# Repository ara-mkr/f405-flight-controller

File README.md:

# F405 Flight Controller

This is a flight controller I designed as a side project. It was fun and pretty challenging, and I'm planning to build a drone with it at some point!

## The design

I did the schematic and layout in KiCad, and wrote some Python scripts to check the connections and spit out the manufacturing files.

It's built around an STM32F405. It reads the gyro and barometer and sends signals out to the ESCs. It also has its own power regulators and plugs for a receiver, GPS, and camera.

I haven't gotten it made or flown yet, so there's still a lot of building and testing to do. If you want to order one, here's [how I'd do it](HOW_TO_ORDER.md).

<table>
<tr>
<td width="50%"><br>Angled view</td>
<td width="50%"><br>Bottom view</td>
</tr>
<tr>
<td><br>Copper layers</td>
<td><br><a href="production/fc_f405_schematic.pdf">Schematic</a></td>
</tr>
</table>

Design files are in [hardware/](hardware/) and the manufacturing stuff is in [production/](production/).

Licensed under [CERN-OHL-P-2.0](LICENSE).

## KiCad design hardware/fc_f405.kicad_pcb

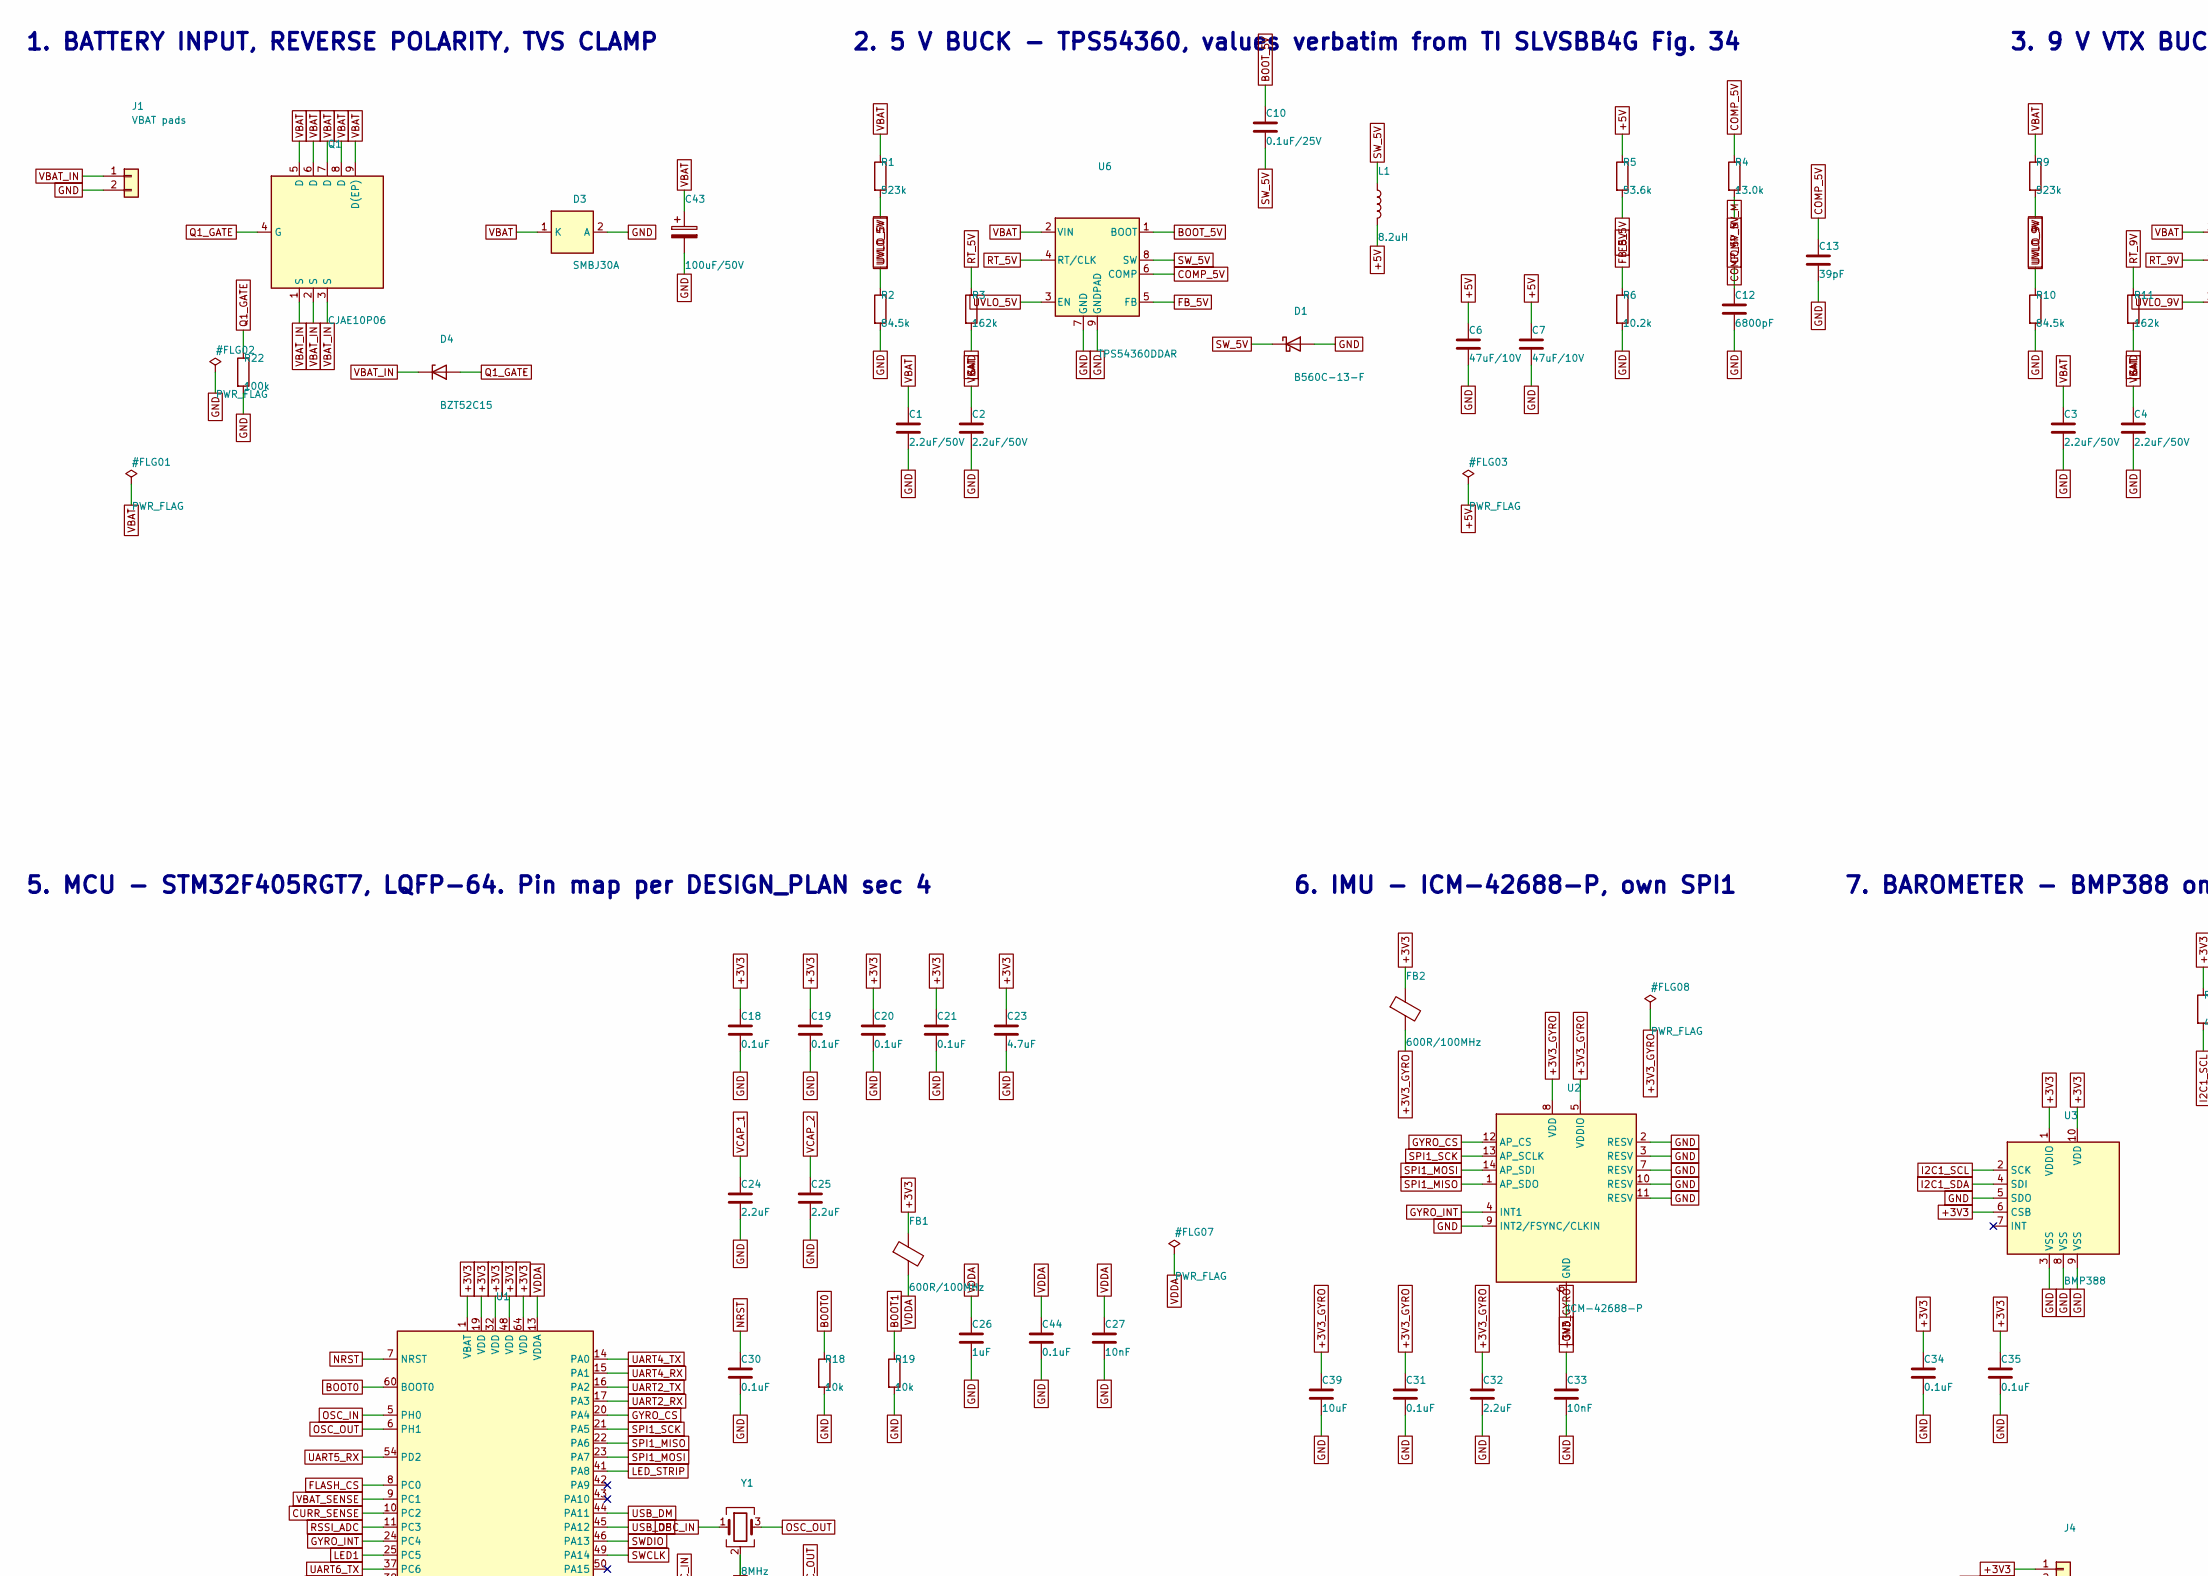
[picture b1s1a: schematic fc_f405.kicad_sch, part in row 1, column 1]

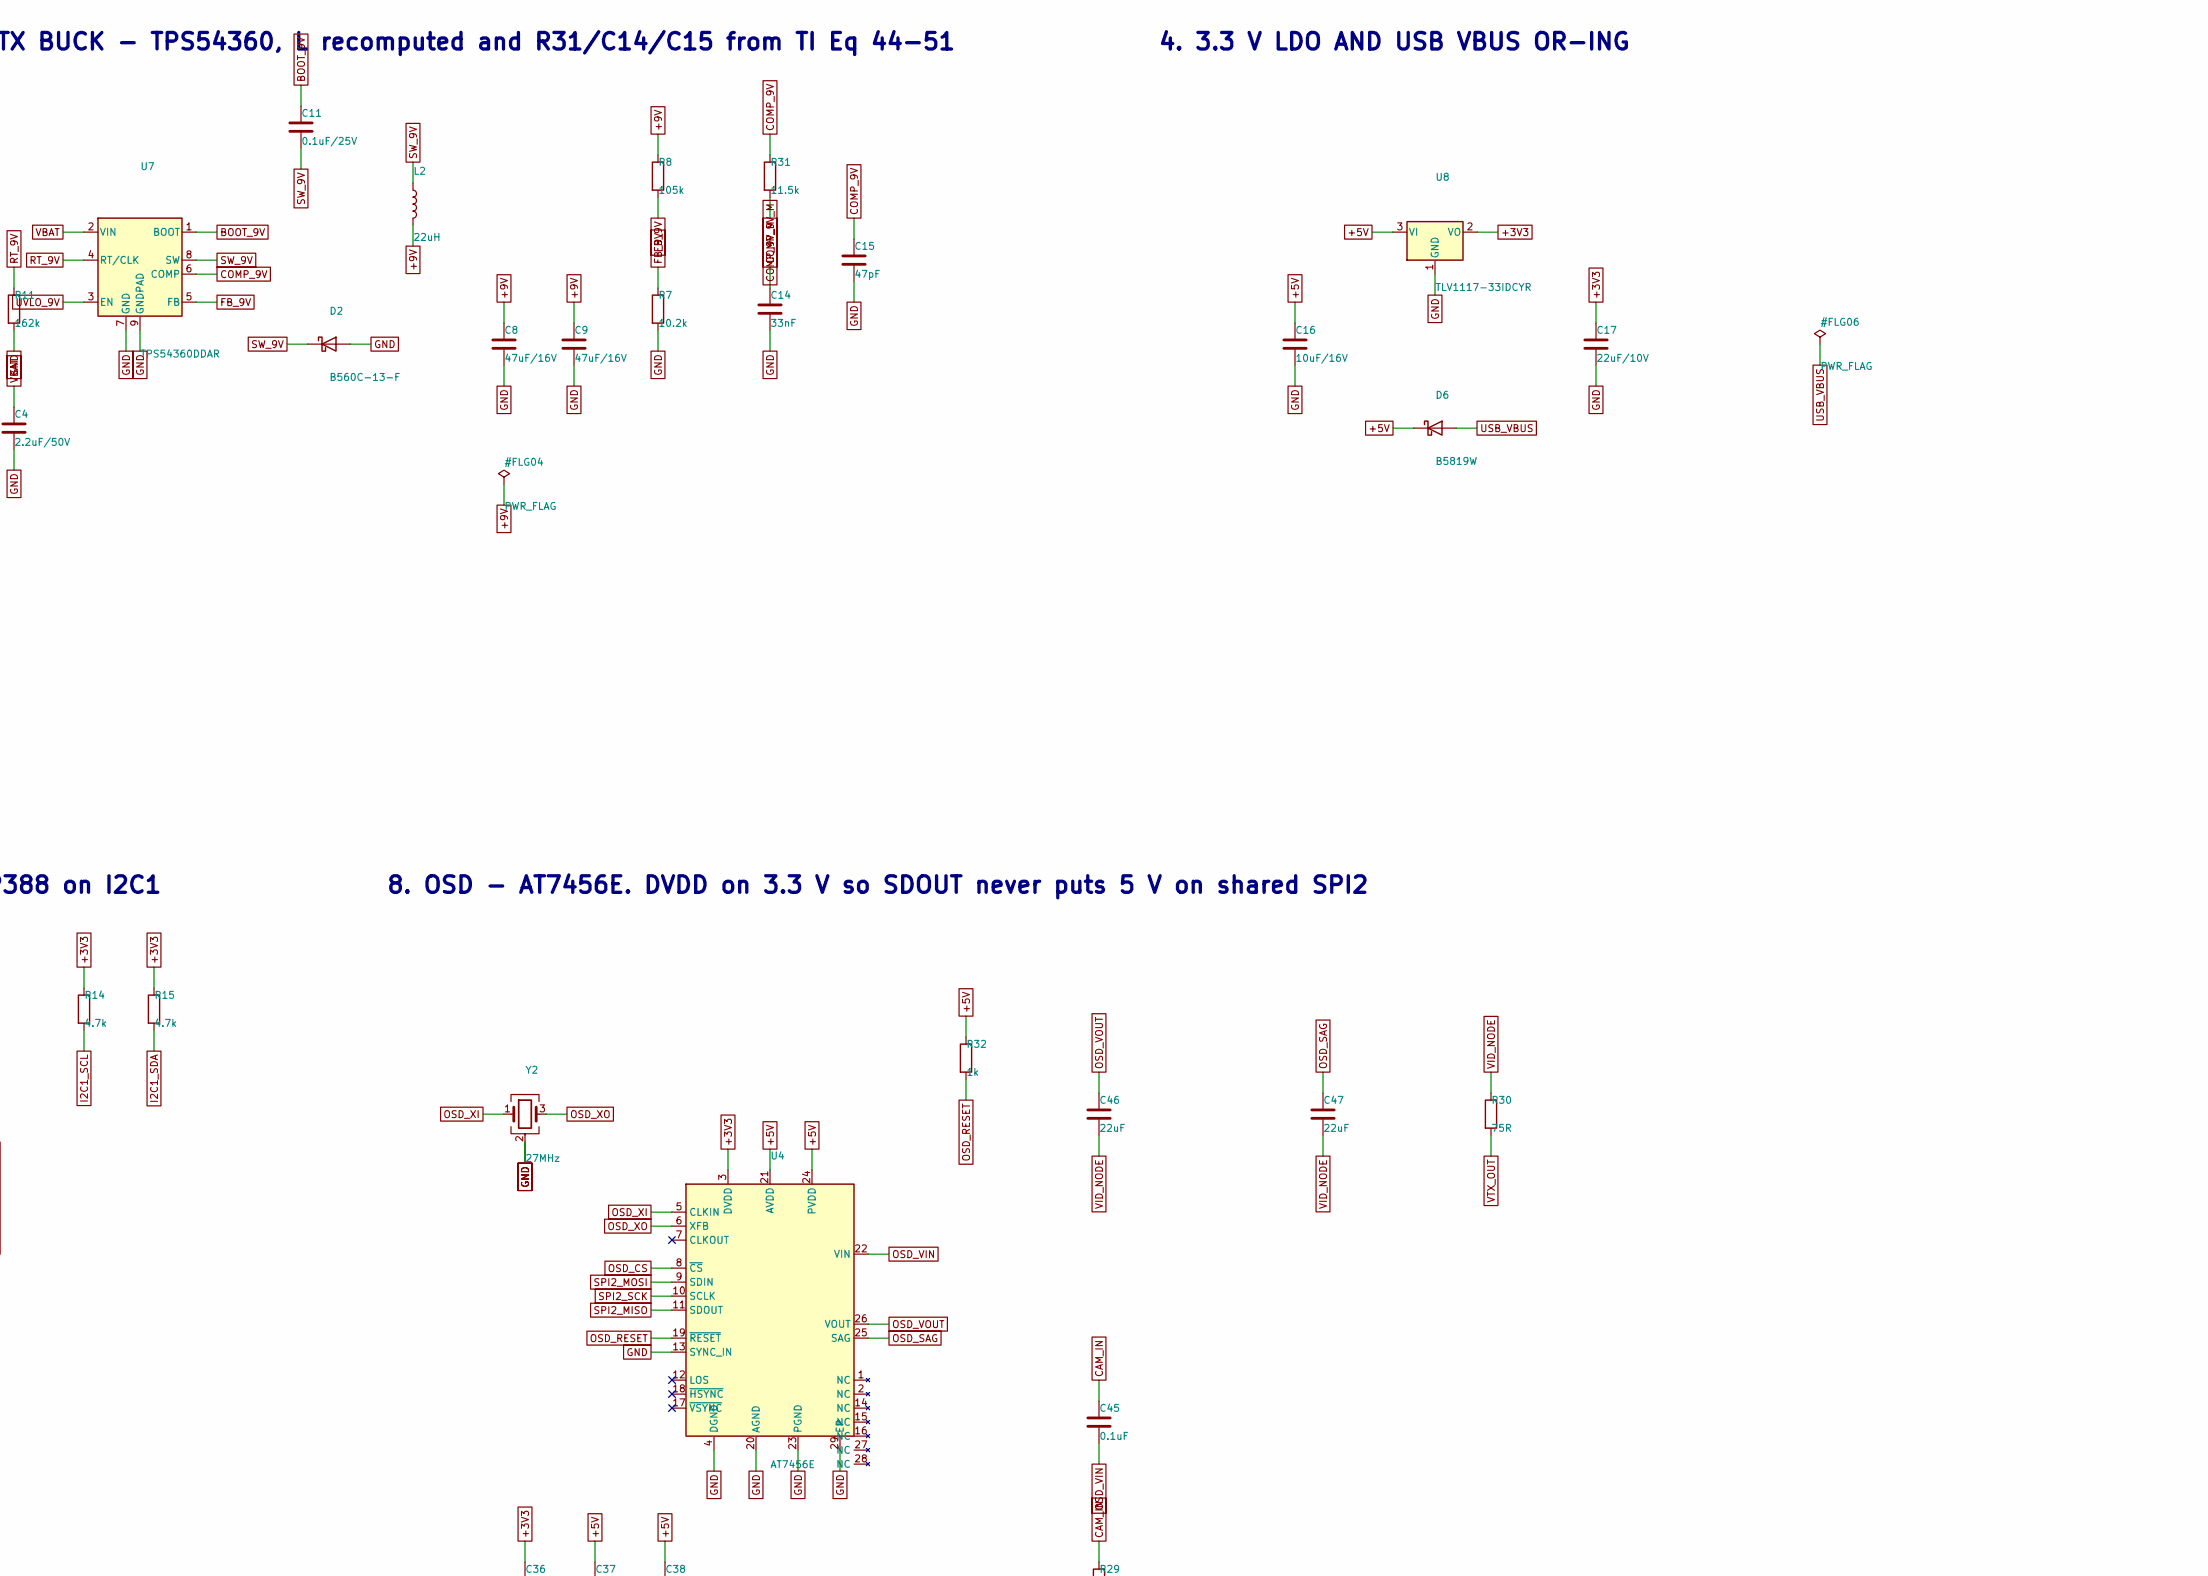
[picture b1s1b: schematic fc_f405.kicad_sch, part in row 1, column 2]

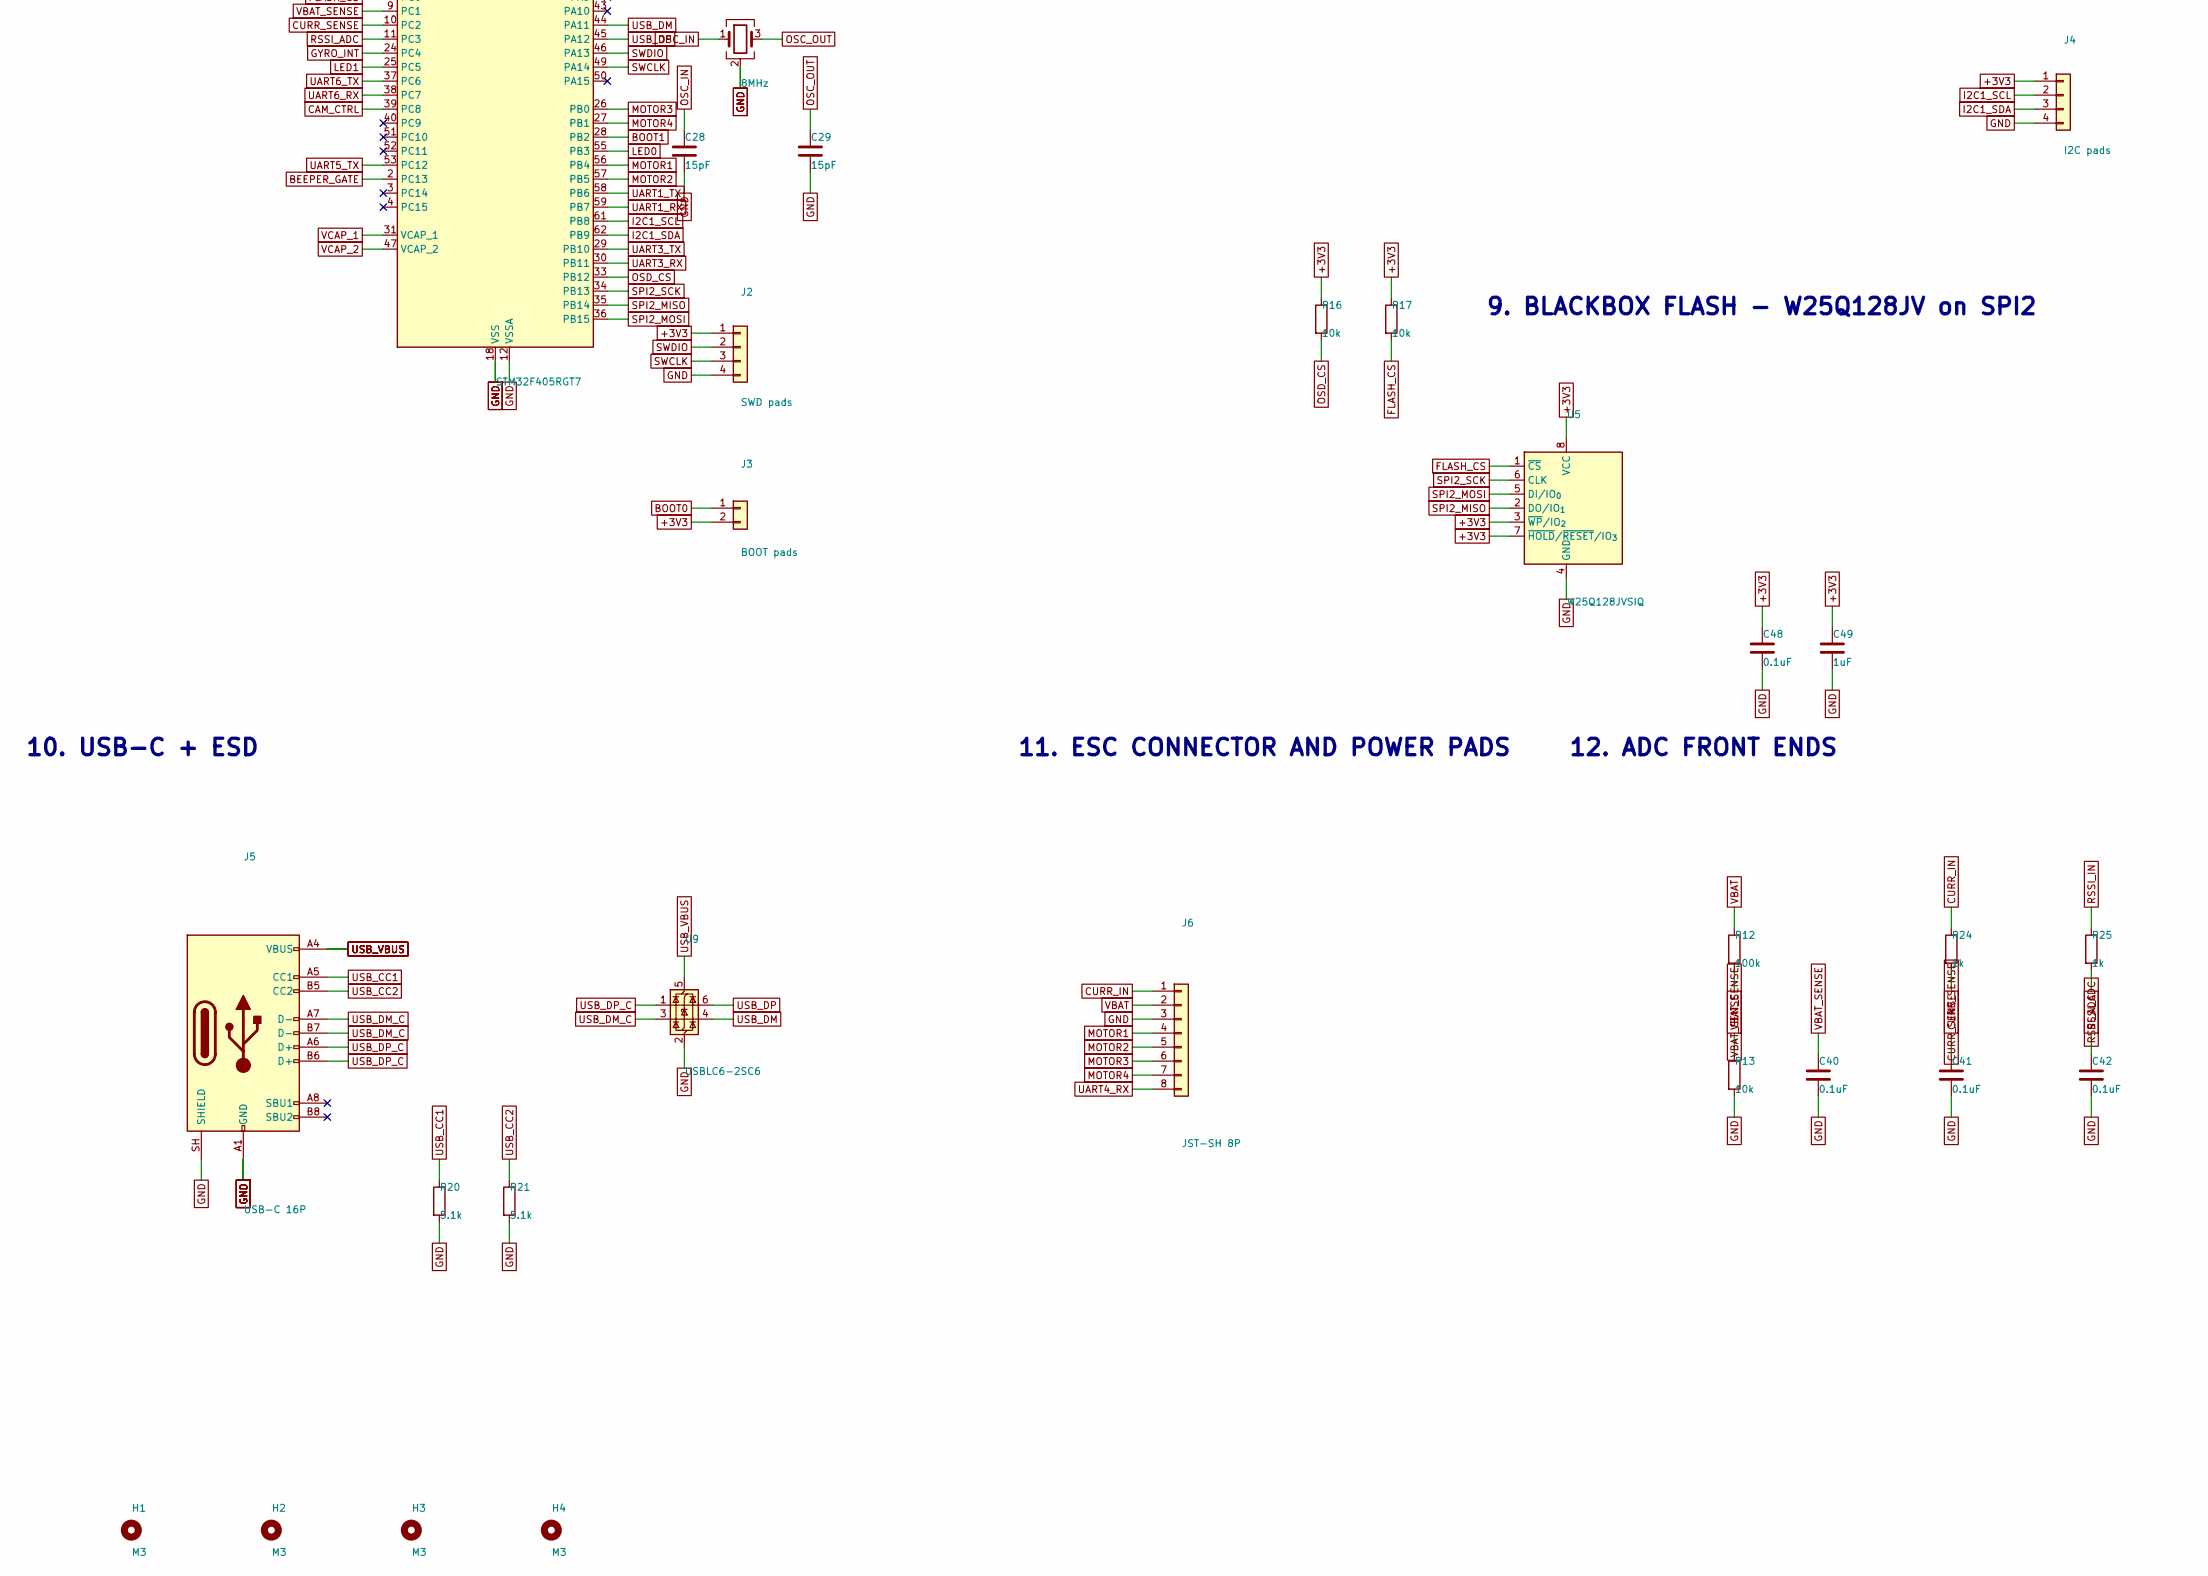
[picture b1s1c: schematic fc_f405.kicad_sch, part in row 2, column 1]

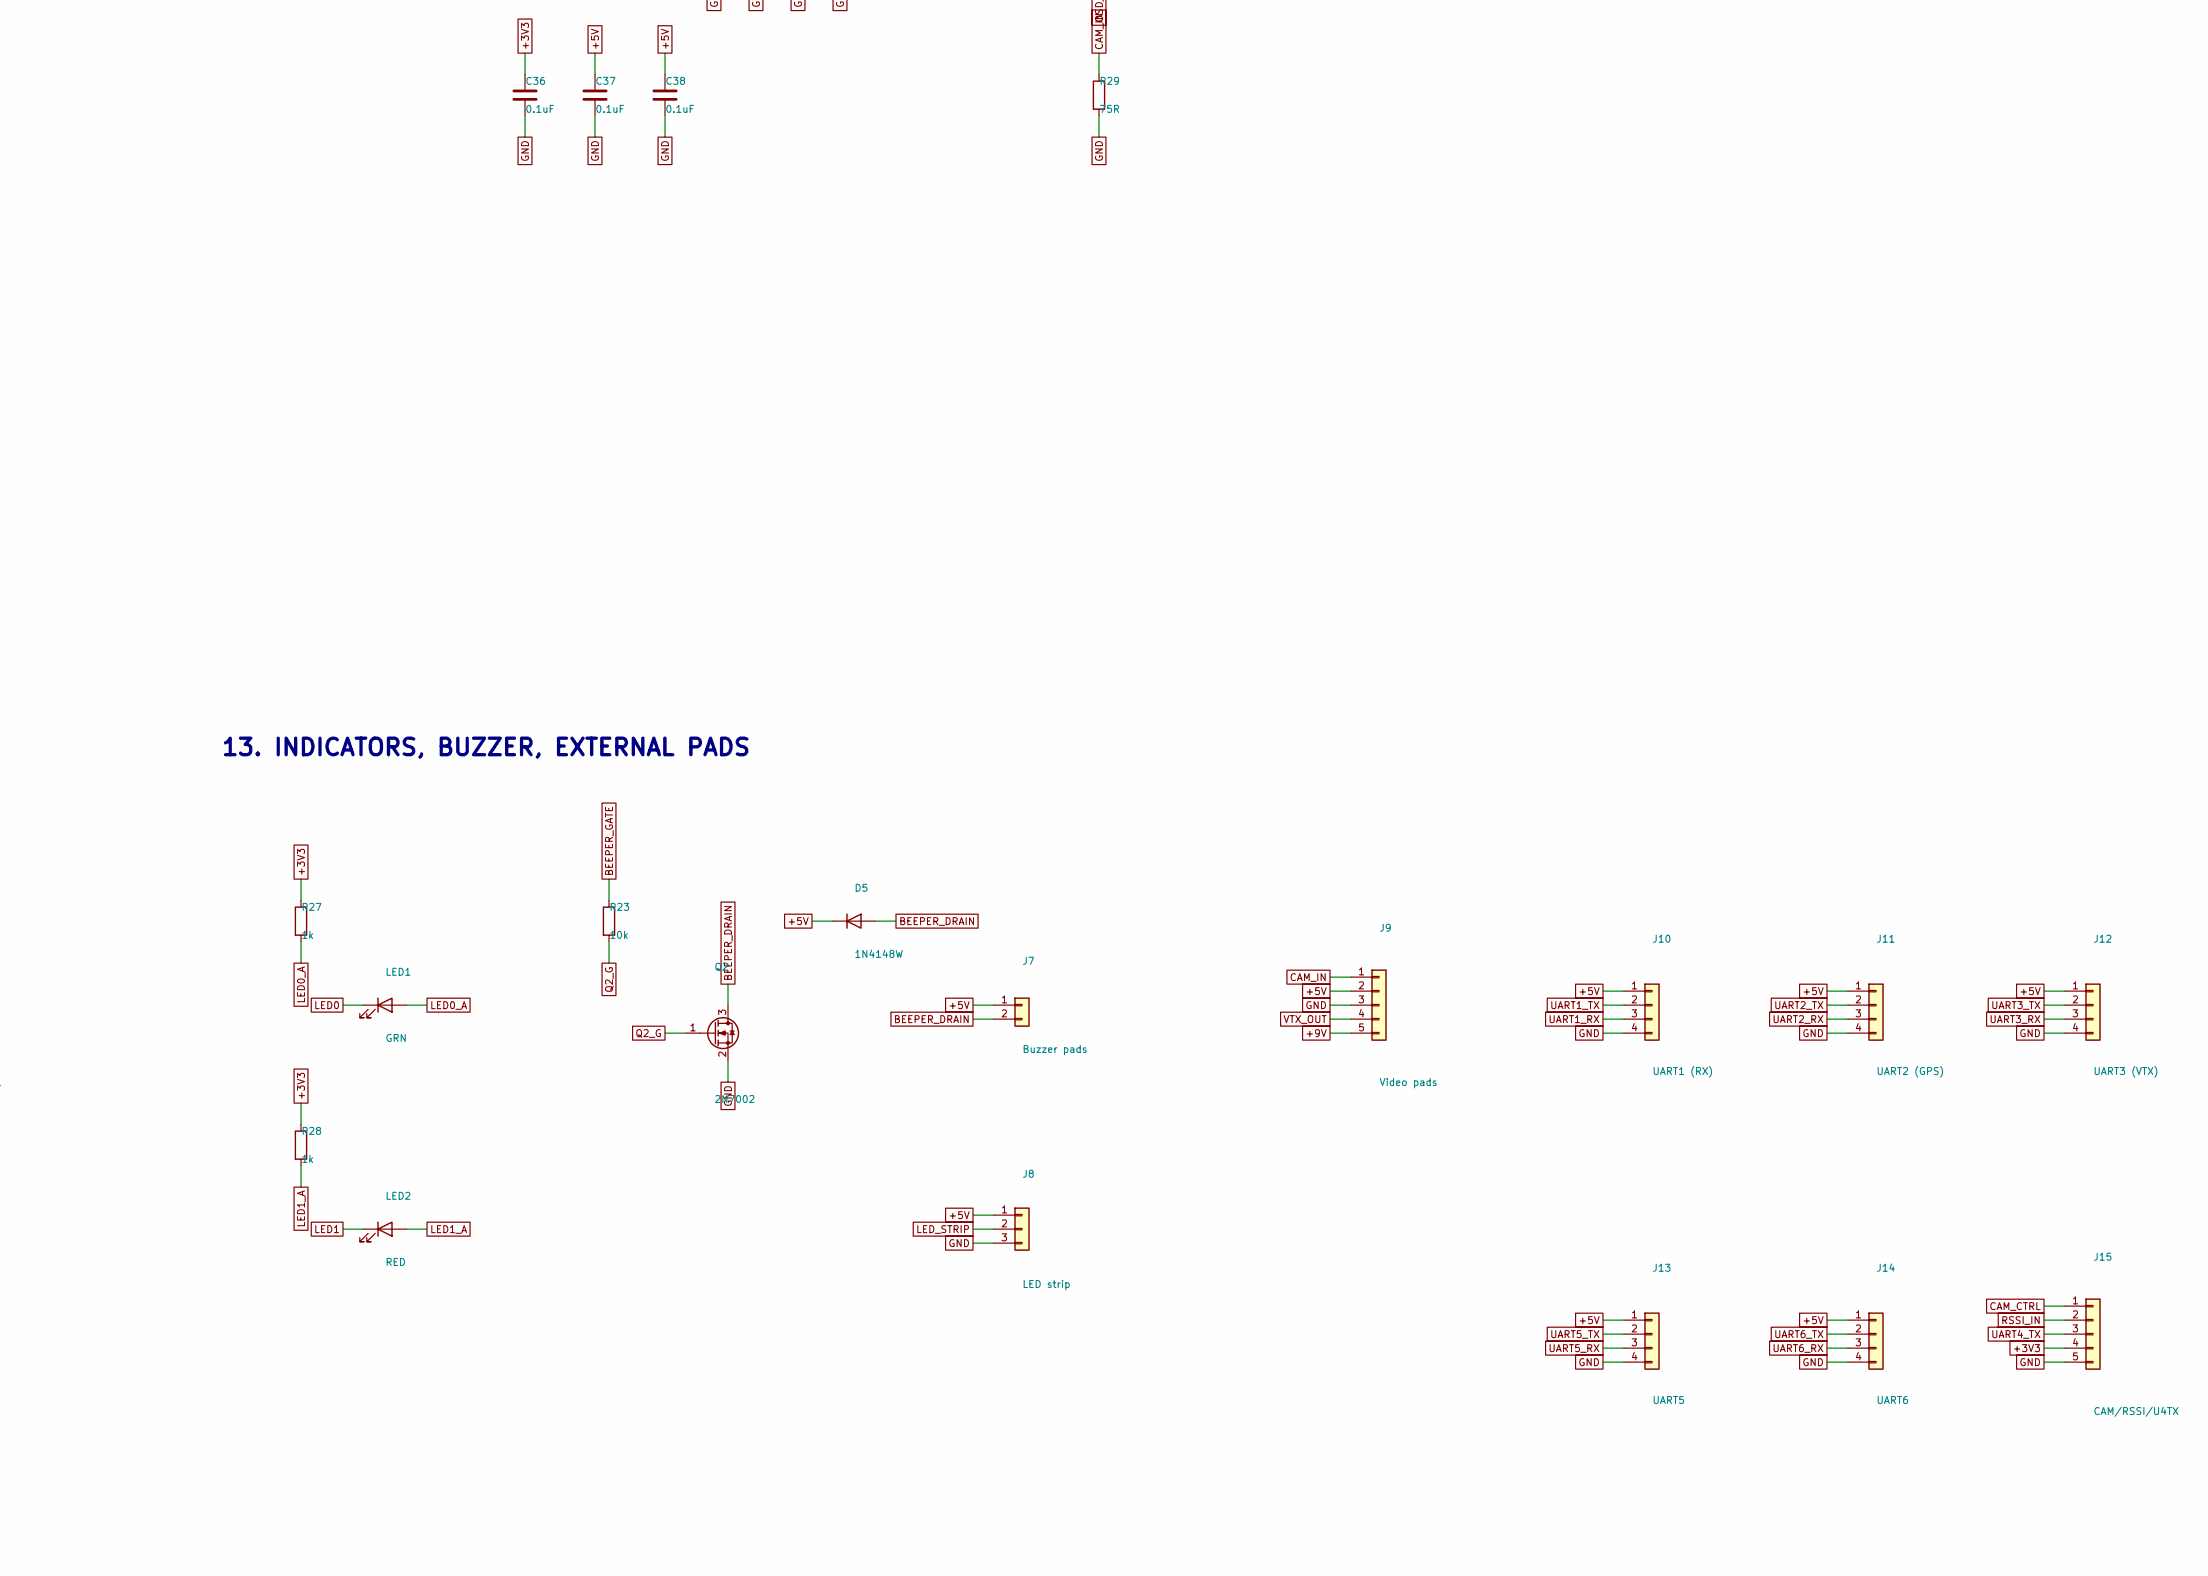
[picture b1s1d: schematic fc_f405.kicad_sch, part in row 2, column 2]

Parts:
C1, C2, C3, C4: 2.2uF/50V; C_1210_3225Metric; MPN 1210B225K500NT; LCSC C1950
C6, C7: 47uF/10V; C_1210_3225Metric; MPN CS3225X7R476K100NRL; LCSC C5189825
C8, C9: 47uF/16V; C_1210_3225Metric; MPN CS3225X7R476K160NRL; LCSC C5440143
C10, C11: 0.1uF/25V; C_0603_1608Metric; MPN CC0603KRX7R9BB104; LCSC C14663
C12: 6800pF; C_0402_1005Metric; MPN 0402B682K500NT; LCSC C1542
C13: 39pF; C_0402_1005Metric; MPN 0402CG390J500NT; LCSC C1563
C14: 33nF; C_0402_1005Metric; MPN 0402B333K500NT; LCSC C507072
C15: 47pF; C_0402_1005Metric; MPN 0402CG470J500NT; LCSC C1567
C16: 10uF/16V; C_0805_2012Metric; MPN GRM21BZ71C106KE15L; LCSC C162430
C17: 22uF/10V; C_0805_2012Metric; MPN CL21A226MAQNNNE; LCSC C45783
C18, C19, C20, C21, C30, C31, C34, C35, C36, C37, C38, C40, C41, C42, C44, C45, C48: 0.1uF; C_0402_1005Metric; MPN CL05B104KO5NNNC; LCSC C1525
C23: 4.7uF; C_0603_1608Metric; MPN GRM188Z71C475KE21D; LCSC C389010
C24, C25, C32: 2.2uF; C_0603_1608Metric; MPN GRM188R71A225KE15D; LCSC C86018
C26, C49: 1uF; C_0402_1005Metric; MPN GRM155R70J105KA12D; LCSC C88945
C27, C33: 10nF; C_0402_1005Metric; MPN CL05B103KB5NNNC; LCSC C15195
C28, C29: 15pF; C_0402_1005Metric; MPN 0402CG150J500NT; LCSC C1548
C39: 10uF; C_0603_1608Metric; MPN CL10A106KP8NNNC; LCSC C19702
C43: 100uF/50V; CP_Elec_8x10.5; MPN UUD1H101MNL1GS; LCSC C116241
C46, C47: 22uF; C_0805_2012Metric; MPN CL21A226MAQNNNE; LCSC C45783
D1, D2: B560C-13-F; D_SMC; MPN B560C-13-F; LCSC C85100
D3: SMBJ30A; D_SMB; MPN SMBJ30A; LCSC C19077584
D4: BZT52C15; D_SOD-123; MPN BZT52C15; LCSC C2932746
D5: 1N4148W; D_SOD-123; MPN 1N4148W; LCSC C81598
D6: B5819W; D_SOD-123; MPN B5819W SL; LCSC C8598
FB1, FB2: 600R/100MHz; R_0603_1608Metric; MPN GZ1608D601TF; LCSC C1002
H1, H2, H3, H4: M3; MountingHole_4.0mm
J1: VBAT pads; SolderPad_3mm_x2; MPN Dia 3mm plated pads
J2: SWD pads; SolderPad_1mm_x4; MPN 1.0mm pads
J3: BOOT pads; SolderPad_1mm_x2; MPN 1.0mm pads
J4: I2C pads; SolderPad_1mm_x4; MPN ext compass
J5: USB-C 16P; USB_C_Receptacle_HRO_TYPE-C-31-M-12; MPN TYPE-C 16PIN 2MD(073); LCSC C2765186
J6: JST-SH 8P; JST_SH_SM08B-SRSS-TB_1x08-1MP_P1.00mm_Horizontal; MPN SM08B-SRSS-TB(LF)(SN); LCSC C160407
J7: Buzzer pads; SolderPad_1mm_x2
J8: LED strip; SolderPad_1mm_x3
J9: Video pads; SolderPad_1mm_x5
J10: UART1 (RX); SolderPad_1mm_x4
J11: UART2 (GPS); SolderPad_1mm_x4
J12: UART3 (VTX); SolderPad_1mm_x4
J13: UART5; SolderPad_1mm_x4
J14: UART6; SolderPad_1mm_x4
J15: CAM/RSSI/U4TX; SolderPad_1mm_x5
L1: 8.2uH; L_SMMS0630_7.1x6.6mm; MPN SMMS0630-8R2M; LCSC C128691
L2: 22uH; L_SMMS0630_7.1x6.6mm; MPN SMMS0630-220M; LCSC C128694
LED1: GRN; LED_0603_1608Metric; MPN XL-1608UGC-04; LCSC C965804
LED2: RED; LED_0603_1608Metric; MPN XL-1608SURC-06; LCSC C965799
Q1: CJAE10P06; PDFNWB-8L_3x3mm_DrainPad; MPN CJAE10P06; LCSC C2943210
Q2: 2N7002; SOT-23; MPN 2N7002K; LCSC C414015
R1, R9: 523k; R_0603_1608Metric; MPN FRC0603F5233TS; LCSC C5126197
R2, R10: 84.5k; R_0603_1608Metric; MPN FRC0603F8452TS; LCSC C2998081
R3, R11: 162k; R_0603_1608Metric; MPN FRC0603F1623TS; LCSC C2998114
R4: 13.0k; R_0603_1608Metric; MPN 0603WAF1302T5E; LCSC C22797
R5: 53.6k; R_0603_1608Metric; MPN FRC0603F5362TS; LCSC C2930115
R6, R7: 10.2k; R_0603_1608Metric; MPN FRC0603F1022TS; LCSC C2933125
R8: 105k; R_0603_1608Metric; MPN FRC0402F1053TS; LCSC C2933067
R12, R22: 100k; R_0402_1005Metric; MPN 0402WGF1003TCE; LCSC C25741
R13, R16, R17, R18, R19, R23: 10k; R_0402_1005Metric; MPN 0402WGF1002TCE; LCSC C25744
R14, R15: 4.7k; R_0402_1005Metric; MPN 0402WGF4701TCE; LCSC C25900
R20, R21: 5.1k; R_0402_1005Metric; MPN 0402WGF5101TCE; LCSC C25905
R24, R25, R27, R28, R32: 1k; R_0402_1005Metric; MPN 0402WGF1001TCE; LCSC C11702
R29, R30: 75R; R_0402_1005Metric; MPN 0402WGF750JTCE; LCSC C25133
R31: 11.5k; R_0603_1608Metric; MPN 0603WAF1152T5E; LCSC C25949
U1: STM32F405RGT7; LQFP-64_10x10mm_P0.5mm; MPN STM32F405RGT7; LCSC C1337199
U2: ICM-42688-P; TDK_LGA-14_2.5x3.0mm; MPN ICM-42688-P; LCSC C1850418
U3: BMP388; Bosch_LGA-10_2.0x2.0mm; MPN BMP388; LCSC C779278
U4: AT7456E; HTSSOP-28-1EP_4.4x9.7mm_P0.65mm_EP2.85x5.4mm; MPN AT7456E; LCSC C82351
U5: W25Q128JVSIQ; SOIC-8_5.3x5.3mm_P1.27mm; MPN W25Q128JVSIQ; LCSC C97521
U6, U7: TPS54360DDAR; SOIC-8-1EP_3.9x4.9mm_P1.27mm_EP2.95x4.9mm_Mask2.71x3.4mm; MPN TPS54360DDAR; LCSC C44377
U8: TLV1117-33IDCYR; SOT-223-3_TabPin2; MPN TLV1117-33IDCYR; LCSC C37359
U9: USBLC6-2SC6; SOT-23-6; MPN USBLC6-2SC6; LCSC C2687116
Y1: 8MHz; Crystal_SMD_3225-4Pin_3.2x2.5mm; MPN TAXM8M4RDBCCT2T; LCSC C400090
Y2: 27MHz; Crystal_SMD_3225-4Pin_3.2x2.5mm; MPN XL2EL89CMI-111YLC-27M; LCSC C19711726

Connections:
+3V3: C17.1, C18.1, C19.1, C20.1, C21.1, C23.1, C34.1, C35.1, C36.1, C48.1, C49.1, FB1.1, FB2.1, J2.1, J3.2, J4.1, J15.4, R14.1, R15.1, R16.1, R17.1, R27.1, R28.1, U1.1 (VBAT), U1.19 (VDD), U1.32 (VDD), U1.48 (VDD), U1.64 (VDD), U3.1 (VDDIO), U3.6 (CSB), U3.10 (VDD), U4.3 (DVDD), U5.3 (~WP/IO_{2}), U5.7 (~HOLD/~RESET/IO_{3}), U5.8 (VCC), U8.2 (VO)
+3V3_GYRO: C31.1, C32.1, C33.1, C39.1, FB2.2, U2.5 (VDDIO), U2.8 (VDD)
+5V: C6.1, C7.1, C16.1, C37.1, C38.1, D5.1 (K), D6.1 (K), J7.1, J8.1, J9.2, J10.1, J11.1, J12.1, J13.1, J14.1, L1.2, R5.1, R32.1, U4.21 (AVDD), U4.24 (PVDD), U8.3 (VI)
+9V: C8.1, C9.1, J9.5, L2.2, R8.1
BEEPER_DRAIN: D5.2 (A), J7.2, Q2.3 (D)
BEEPER_GATE: R23.1, U1.2 (PC13)
BOOT0: J3.1, R18.1, U1.60 (BOOT0)
BOOT1: R19.1, U1.28 (PB2)
BOOT_5V: C10.1, U6.1 (BOOT)
BOOT_9V: C11.1, U7.1 (BOOT)
CAM_CTRL: J15.1, U1.39 (PC8)
CAM_IN: C45.1, J9.1, R29.1
COMP_5V: C13.1, R4.1, U6.6 (COMP)
COMP_5V_M: C12.1, R4.2
COMP_9V: C15.1, R31.1, U7.6 (COMP)
COMP_9V_M: C14.1, R31.2
CURR_IN: J6.1, R24.1
CURR_SENSE: C41.1, R24.2, U1.10 (PC2)
FB_5V: R5.2, R6.1, U6.5 (FB)
FB_9V: R7.1, R8.2, U7.5 (FB)
FLASH_CS: R17.2, U1.8 (PC0), U5.1 (~CS)
GND: C1.2, C2.2, C3.2, C4.2, C6.2, C7.2, C8.2, C9.2, C12.2, C13.2, C14.2, C15.2, C16.2, C17.2, C18.2, C19.2, C20.2, C21.2, C23.2, C24.2, C25.2, C26.2, C27.2, C28.2, C29.2, C30.2, C31.2, C32.2, C33.2, C34.2, C35.2, C36.2, C37.2, C38.2, C39.2, C40.2, C41.2, C42.2, C43.2, C44.2, C48.2, C49.2, D1.2 (A), D2.2 (A), D3.2 (A), J1.2, J2.4, J4.4, J5.A1 (GND), J5.A12 (GND), J5.B1 (GND), J5.B12 (GND), J5.SH (SHIELD), J6.3, J8.3, J9.3, J10.4, J11.4, J12.4, J13.4, J14.4, J15.5, Q2.2 (S), R2.2, R3.2, R6.2, R7.2, R10.2, R11.2, R13.2, R18.2, R19.2, R20.2, R21.2, R22.2, R29.2, U1.12 (VSSA), U1.18 (VSS), U1.63 (VSS), U2.2 (RESV), U2.3 (RESV), U2.6 (GND), U2.7 (RESV), U2.9 (INT2/FSYNC/CLKIN), U2.10 (RESV), U2.11 (RESV), U3.3 (VSS), U3.5 (SDO), U3.8 (VSS), U3.9 (VSS), U4.4 (DGND), U4.13 (SYNC_IN), U4.20 (AGND), U4.23 (PGND), U4.29 (EP), U5.4 (GND), U6.7 (GND), U6.9 (GNDPAD), U7.7 (GND), U7.9 (GNDPAD), U8.1 (GND), U9.2 (GND), Y1.2 (G), Y1.4 (G), Y2.2 (G), Y2.4 (G)
GYRO_CS: U1.20 (PA4), U2.12 (AP_CS)
GYRO_INT: U1.24 (PC4), U2.4 (INT1)
I2C1_SCL: J4.2, R14.2, U1.61 (PB8), U3.2 (SCK)
I2C1_SDA: J4.3, R15.2, U1.62 (PB9), U3.4 (SDI)
LED0: LED1.1 (K), U1.55 (PB3)
LED0_A: LED1.2 (A), R27.2
LED1: LED2.1 (K), U1.25 (PC5)
LED1_A: LED2.2 (A), R28.2
LED_STRIP: J8.2, U1.41 (PA8)
MOTOR1: J6.4, U1.56 (PB4)
MOTOR2: J6.5, U1.57 (PB5)
MOTOR3: J6.6, U1.26 (PB0)
MOTOR4: J6.7, U1.27 (PB1)
NRST: C30.1, U1.7 (NRST)
OSC_IN: C28.1, U1.5 (PH0), Y1.1
OSC_OUT: C29.1, U1.6 (PH1), Y1.3
OSD_CS: R16.2, U1.33 (PB12), U4.8 (~CS)
OSD_RESET: R32.2, U4.19 (~RESET)
OSD_SAG: C47.1, U4.25 (SAG)
OSD_VIN: C45.2, U4.22 (VIN)
OSD_VOUT: C46.1, U4.26 (VOUT)
OSD_XI: U4.5 (CLKIN), Y2.1
OSD_XO: U4.6 (XFB), Y2.3
Q1_GATE: D4.2 (A), Q1.4 (G), R22.1
Q2_G: Q2.1 (G), R23.2
RSSI_ADC: C42.1, R25.2, U1.11 (PC3)
RSSI_IN: J15.2, R25.1
RT_5V: R3.1, U6.4 (RT/CLK)
RT_9V: R11.1, U7.4 (RT/CLK)
SPI1_MISO: U1.22 (PA6), U2.1 (AP_SDO)
SPI1_MOSI: U1.23 (PA7), U2.14 (AP_SDI)
SPI1_SCK: U1.21 (PA5), U2.13 (AP_SCLK)
SPI2_MISO: U1.35 (PB14), U4.11 (SDOUT), U5.2 (DO/IO_{1})
SPI2_MOSI: U1.36 (PB15), U4.9 (SDIN), U5.5 (DI/IO_{0})
SPI2_SCK: U1.34 (PB13), U4.10 (SCLK), U5.6 (CLK)
SWCLK: J2.3, U1.49 (PA14)
SWDIO: J2.2, U1.46 (PA13)
SW_5V: C10.2, D1.1 (K), L1.1, U6.8 (SW)
SW_9V: C11.2, D2.1 (K), L2.1, U7.8 (SW)
UART1_RX: J10.3, U1.59 (PB7)
UART1_TX: J10.2, U1.58 (PB6)
UART2_RX: J11.3, U1.17 (PA3)
UART2_TX: J11.2, U1.16 (PA2)
UART3_RX: J12.3, U1.30 (PB11)
UART3_TX: J12.2, U1.29 (PB10)
UART4_RX: J6.8, U1.15 (PA1)
UART4_TX: J15.3, U1.14 (PA0)
UART5_RX: J13.3, U1.54 (PD2)
UART5_TX: J13.2, U1.53 (PC12)
UART6_RX: J14.3, U1.38 (PC7)
UART6_TX: J14.2, U1.37 (PC6)
USB_CC1: J5.A5 (CC1), R20.1
USB_CC2: J5.B5 (CC2), R21.1
USB_DM: U1.44 (PA11), U9.4 (I/O2)
USB_DM_C: J5.A7 (D-), J5.B7 (D-), U9.3 (I/O2)
USB_DP: U1.45 (PA12), U9.6 (I/O1)
USB_DP_C: J5.A6 (D+), J5.B6 (D+), U9.1 (I/O1)
USB_VBUS: D6.2 (A), J5.A4 (VBUS), J5.A9 (VBUS), J5.B4 (VBUS), J5.B9 (VBUS), U9.5 (VBUS)
UVLO_5V: R1.2, R2.1, U6.3 (EN)
UVLO_9V: R9.2, R10.1, U7.3 (EN)
VBAT: C1.1, C2.1, C3.1, C4.1, C43.1, D3.1 (K), J6.2, Q1.5 (D), Q1.6 (D), Q1.7 (D), Q1.8 (D), Q1.9 (D(EP)), R1.1, R9.1, R12.1, U6.2 (VIN), U7.2 (VIN)
VBAT_IN: D4.1 (K), J1.1, Q1.1 (S), Q1.2 (S), Q1.3 (S)
VBAT_SENSE: C40.1, R12.2, R13.1, U1.9 (PC1)
VCAP_1: C24.1, U1.31 (VCAP_1)
VCAP_2: C25.1, U1.47 (VCAP_2)
VDDA: C26.1, C27.1, C44.1, FB1.2, U1.13 (VDDA)
VID_NODE: C46.2, C47.2, R30.1
VTX_OUT: J9.4, R30.2

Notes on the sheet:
1. BATTERY INPUT, REVERSE POLARITY, TVS CLAMP
2. 5 V BUCK - TPS54360, values verbatim from TI SLVSBB4G Fig. 34
3. 9 V VTX BUCK - TPS54360, L recomputed and R31/C14/C15 from TI Eq 44-51
4. 3.3 V LDO AND USB VBUS OR-ING
5. MCU - STM32F405RGT7, LQFP-64. Pin map per DESIGN_PLAN sec 4
6. IMU - ICM-42688-P, own SPI1
7. BAROMETER - BMP388 on I2C1
8. OSD - AT7456E. DVDD on 3.3 V so SDOUT never puts 5 V on shared SPI2
9. BLACKBOX FLASH - W25Q128JV on SPI2
10. USB-C + ESD
11. ESC CONNECTOR AND POWER PADS
12. ADC FRONT ENDS
13. INDICATORS, BUZZER, EXTERNAL PADS
